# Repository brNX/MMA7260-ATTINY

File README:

Board for MMA7260 Accelerometer using an ATtiny for I2C/TWI

I2C Device Address 0x26

address 	command 	Type 		description
0x00 		GETVALUE 	Read		device sends 6 bytes (2bytes per axis)
0x01		SETSENS 	Write		set sensivity: 2g send value 2 , 6g send value 6

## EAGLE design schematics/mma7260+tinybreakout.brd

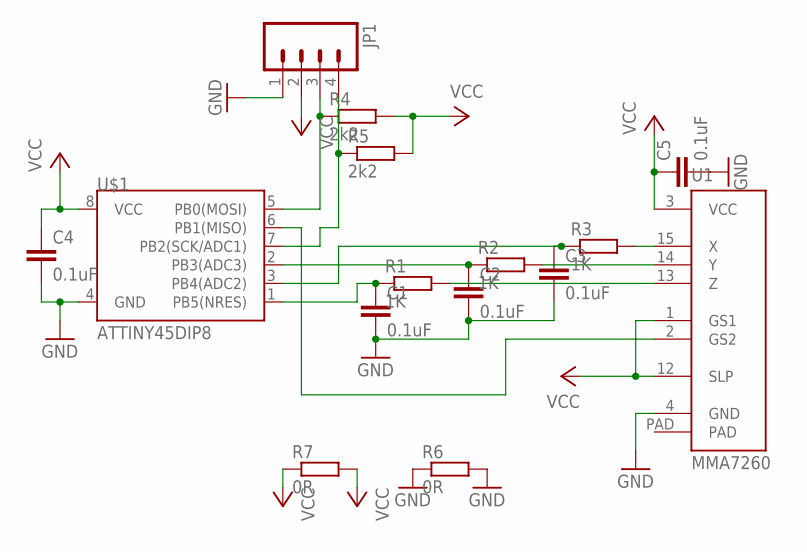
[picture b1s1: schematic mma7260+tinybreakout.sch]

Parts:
C1, C2, C3, C4, C5: 0.1uF; C1206
JP1: M04LOCK; 1X04_LOCK
R1, R2, R3: 1K; R0805
R4, R5: 2k2; R0805
R6, R7: 0R; R1206
U1: MMA7260
U$1: ATTINY45DIP8; DIP08

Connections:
GND: C1.2, C2.2, C3.2, C4.2, C5.2, JP1.1, R6.1, R6.2, U1.4 (GND), U$1.4 (GND)
unnamed: R1.2, U1.13 (Z)
unnamed: R2.2, U1.14 (Y)
unnamed: R3.2, U1.15 (X)
unnamed: C3.1, R3.1, U$1.3 (PB4(ADC2))
unnamed: C2.1, R2.1, U$1.2 (PB3(ADC3))
unnamed: JP1.4, R5.1, U$1.7 (PB2(SCK/ADC1))
unnamed: U1.2 (GS2), U$1.6 (PB1(MISO))
unnamed: C1.1, R1.1, U$1.1 (PB5(NRES))
unnamed: JP1.3, R4.1, U$1.5 (PB0(MOSI))
VCC: C4.1, C5.1, JP1.2, R4.2, R5.2, R7.1, R7.2, U1.1 (GS1), U1.3 (VCC), U1.12 (SLP), U$1.8 (VCC)

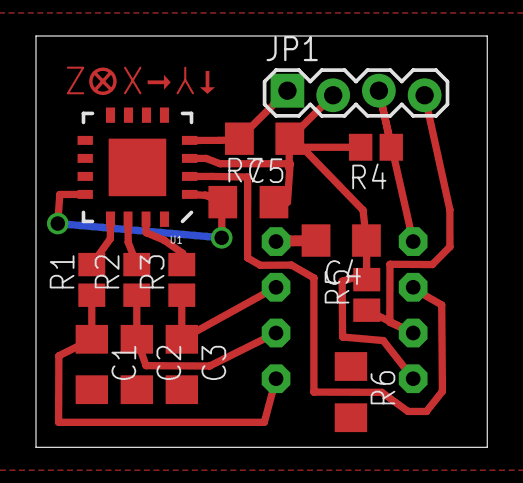
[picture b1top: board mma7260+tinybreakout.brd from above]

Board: 2 copper layers, 25.1 x 22.9 mm, 15 parts (1 on the bottom side), 11 nets.

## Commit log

2012-05-12 twi working @ 16 mhz
2012-05-15 final firmware , schematics
2012-05-16 README
2012-05-22 send the 6 bytes in 1 command (sending 2 byte while reading the next adc channel)
2012-05-22 description
